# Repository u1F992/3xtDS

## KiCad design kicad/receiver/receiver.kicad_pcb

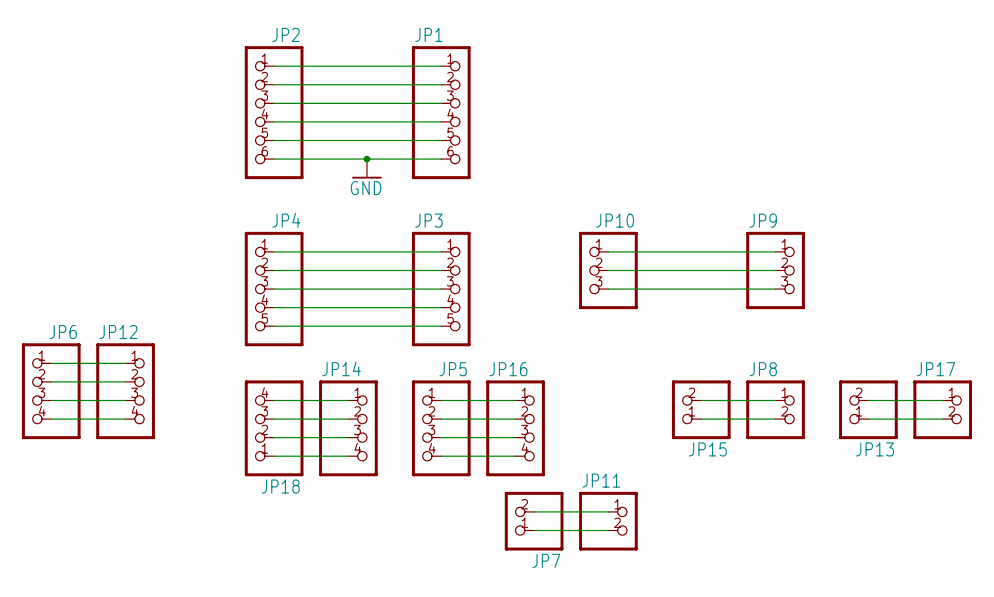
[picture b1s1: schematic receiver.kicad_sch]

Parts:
JP1, JP2: PINHD-1X6; 1X06
JP3, JP4: PINHD-1X5; 1X05
JP5, JP6, JP12, JP14, JP16, JP18: PINHD-1X4; 1X04
JP7, JP8, JP11, JP13, JP15, JP17: PINHD-1X2; 1X02
JP9, JP10: PINHD-1X3; 1X03

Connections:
GND: JP1.6, JP2.6
unnamed: JP1.1, JP2.1
unnamed: JP1.2, JP2.2
unnamed: JP1.3, JP2.3
unnamed: JP1.4, JP2.4
unnamed: JP1.5, JP2.5
unnamed: JP8.1, JP15.2
unnamed: JP3.1, JP4.1
unnamed: JP3.2, JP4.2
unnamed: JP3.3, JP4.3
unnamed: JP3.4, JP4.4
unnamed: JP3.5, JP4.5
unnamed: JP8.2, JP15.1
unnamed: JP7.2, JP11.1
unnamed: JP7.1, JP11.2
unnamed: JP6.1, JP12.1
unnamed: JP6.2, JP12.2
unnamed: JP6.3, JP12.3
unnamed: JP6.4, JP12.4
unnamed: JP5.1, JP16.1
unnamed: JP9.1, JP10.1
unnamed: JP9.2, JP10.2
unnamed: JP9.3, JP10.3
unnamed: JP5.2, JP16.2
unnamed: JP5.3, JP16.3
unnamed: JP5.4, JP16.4
unnamed: JP14.1, JP18.4
unnamed: JP14.2, JP18.3
unnamed: JP14.3, JP18.2
unnamed: JP14.4, JP18.1
unnamed: JP13.2, JP17.1
unnamed: JP13.1, JP17.2

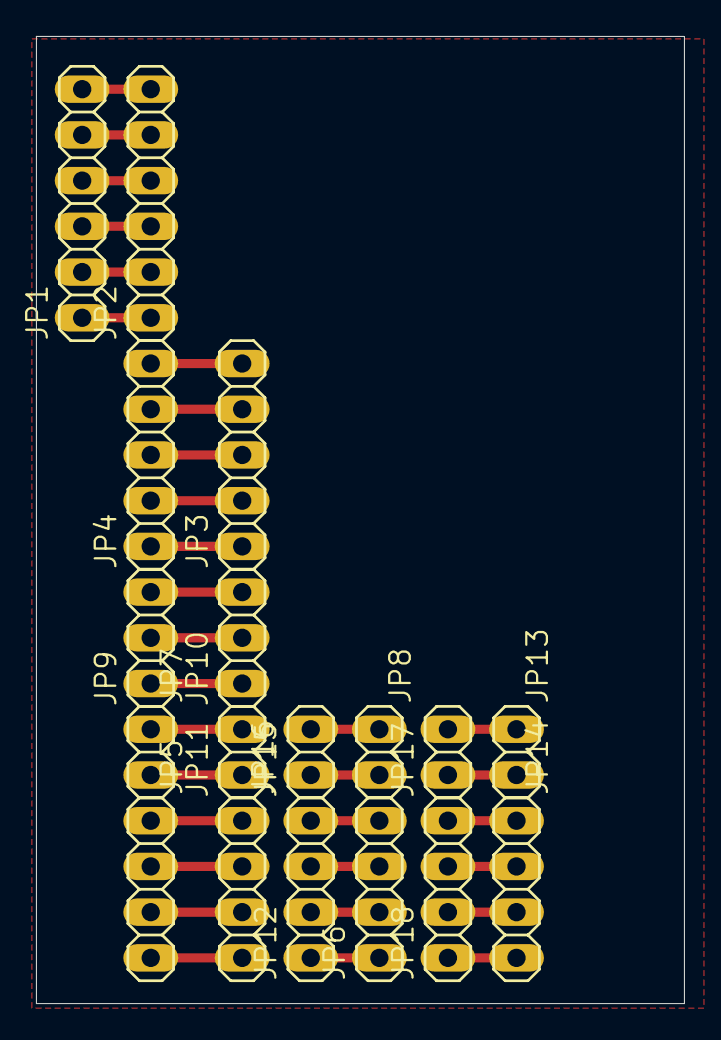
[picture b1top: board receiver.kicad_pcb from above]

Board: 2 copper layers, 36.0 x 53.7 mm, 18 parts (0 on the bottom side), 32 nets.

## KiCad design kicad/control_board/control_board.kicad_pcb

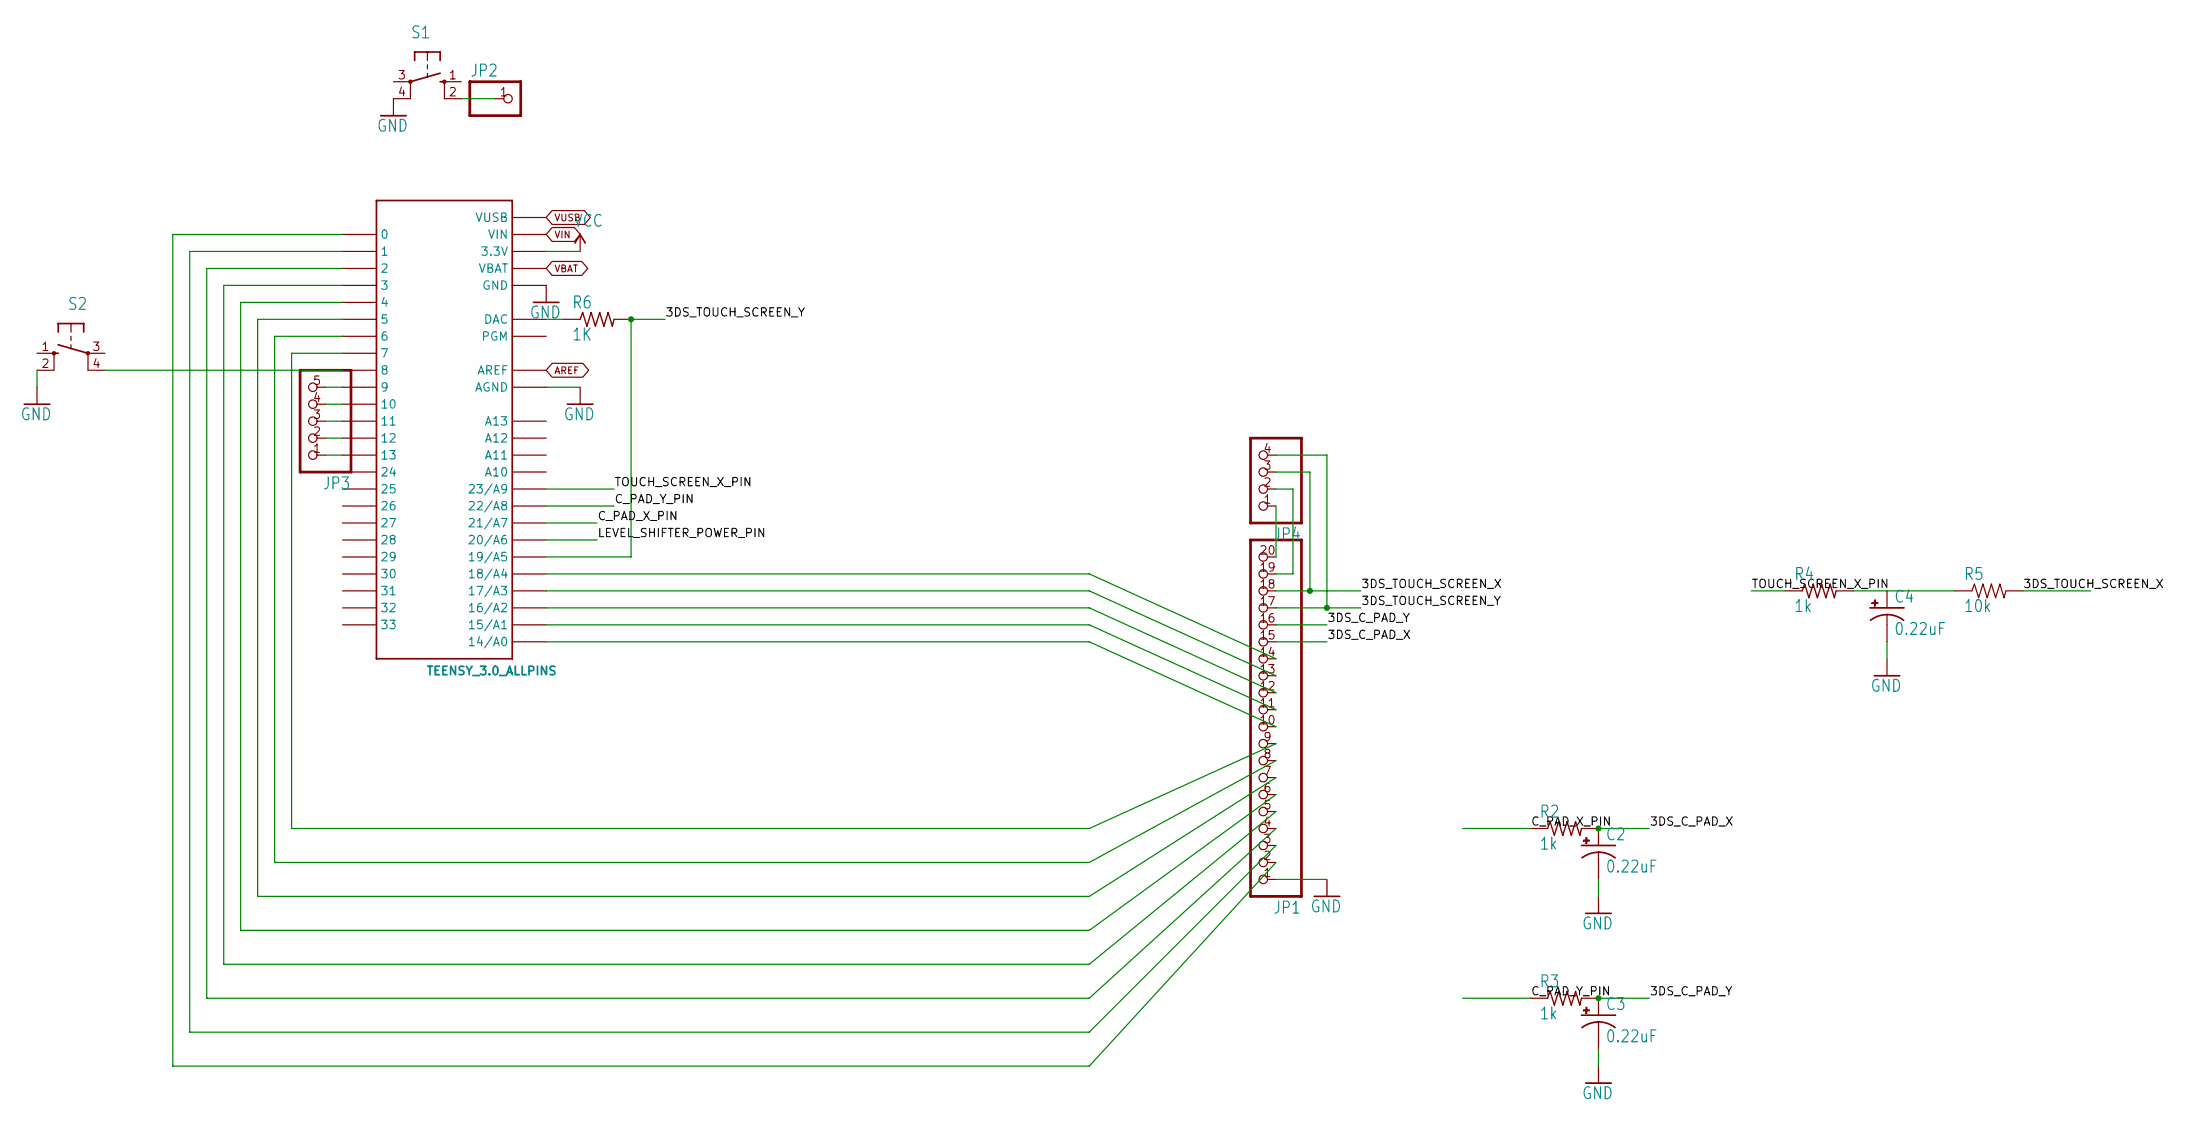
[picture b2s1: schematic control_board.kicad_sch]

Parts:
C2, C3, C4: 0.22uF; CPOL-RADIAL-10UF-25V
JP1: PINHD-1X20; 1X20
JP2: PINHD-1X1; 1X01
JP3: PINHD-1X5; 1X05
JP4: PINHD-1X4; 1X04
R2, R3, R4: 1k; 0207_7
R5: 10k; AXIAL-0.1
R6: 1K; 0207_7
S1, S2: 10-XX; B3F-10XX
U$1: TEENSY_3.0_ALLPINS

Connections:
3DS_C_PAD_X: C2.1 (+), JP1.15, R2.2
3DS_C_PAD_Y: C3.1 (+), JP1.16, R3.2
3DS_TOUCH_SCREEN_X: JP1.18, JP4.3, R5.P$2 (2)
3DS_TOUCH_SCREEN_Y: JP1.17, JP4.4, R6.2, U$1.19/A5
AREF: U$1.AREF
C_PAD_X_PIN: R2.1, U$1.21/A7
C_PAD_Y_PIN: R3.1, U$1.22/A8
GND: C2.2 (-), C3.2 (-), C4.2 (-), JP1.1, S1.4 (P1), S2.2 (S1), U$1.AGND, U$1.GND, U$1.GND1 (GND), U$1.GND2 (GND)
LEVEL_SHIFTER_POWER_PIN: U$1.20/A6
unnamed: JP2.1, S1.2 (S1)
unnamed: JP1.10, U$1.14/A0
unnamed: JP1.11, U$1.15/A1
unnamed: JP1.12, U$1.16/A2
unnamed: JP1.13, U$1.17/A3
unnamed: JP1.2, U$1.0
unnamed: JP1.3, U$1.1
unnamed: JP1.4, U$1.2
unnamed: JP1.5, U$1.3
unnamed: JP1.6, U$1.4
unnamed: JP1.7, U$1.5
unnamed: JP1.8, U$1.6
unnamed: JP1.9, U$1.7
unnamed: R6.1, U$1.RESET (DAC)
unnamed: JP1.14, U$1.18/A4
unnamed: JP3.5, U$1.9
unnamed: JP3.4, U$1.10
unnamed: JP3.3, U$1.11
unnamed: JP3.2, U$1.12
unnamed: JP3.1, U$1.13
unnamed: JP1.20, JP4.1
unnamed: JP1.19, JP4.2
unnamed: S2.4 (P1), U$1.8
TOUCH_SCREEN_X_PIN: R4.1, U$1.23/A9
VBAT: U$1.VBAT
VCC: U$1.3.3V, U$1.3.3V1 (3.3V), U$1.3.3V2 (3.3V)
VIN: U$1.VIN
VUSB: U$1.VUSB

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
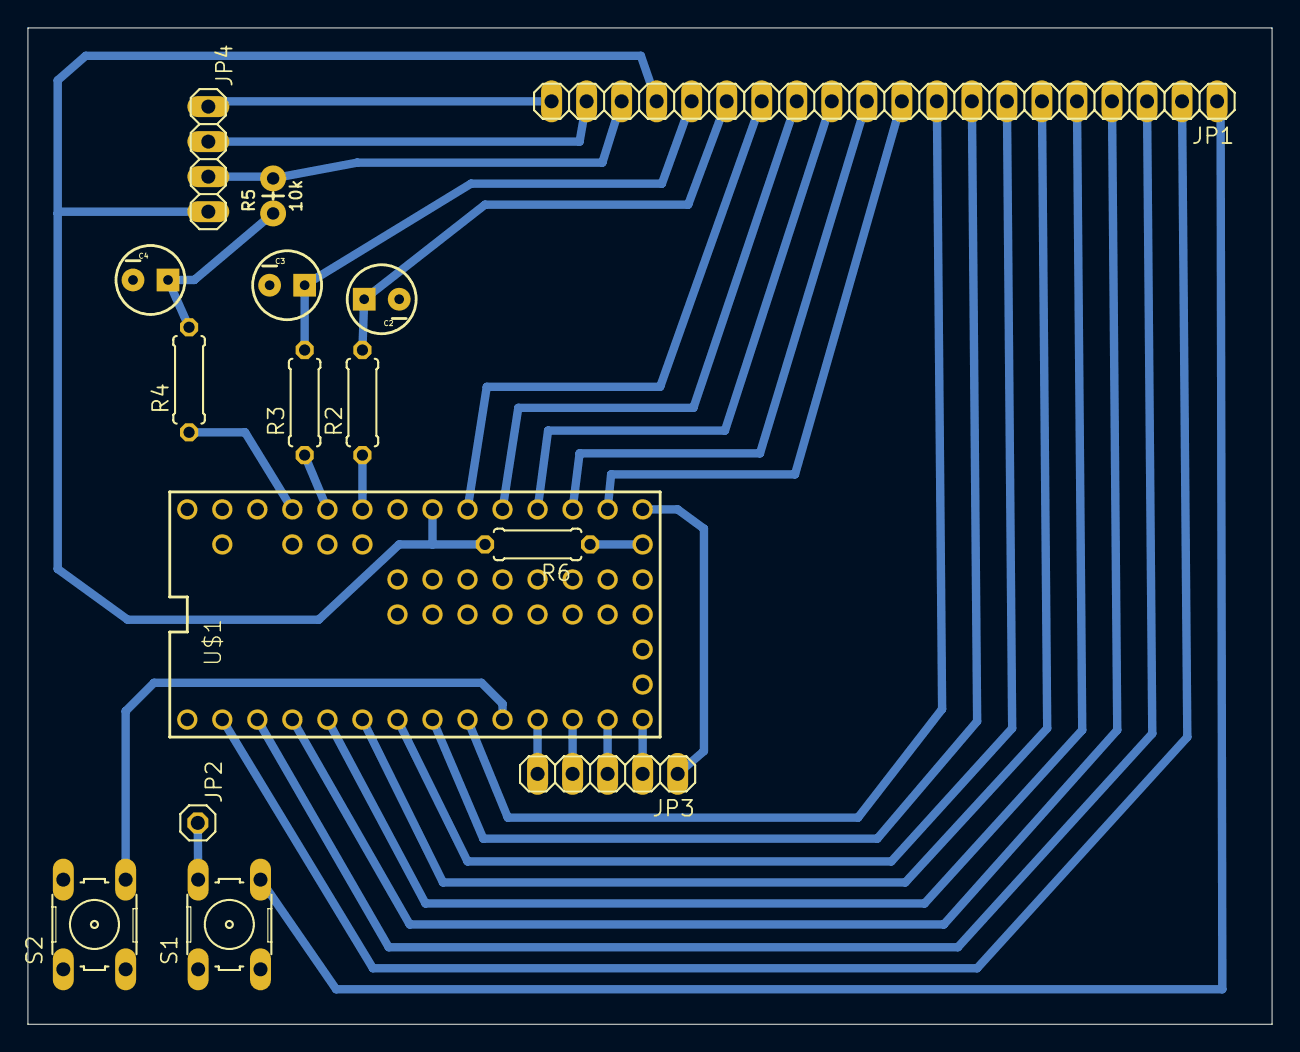
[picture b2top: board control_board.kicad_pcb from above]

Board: 2 copper layers, 90.2 x 72.3 mm, 15 parts (0 on the bottom side), 33 nets.

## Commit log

2023-05-04 Add gitignore
2023-05-04 Add KiCad projects
2023-05-04 Add Japanese version of overview.pdf
